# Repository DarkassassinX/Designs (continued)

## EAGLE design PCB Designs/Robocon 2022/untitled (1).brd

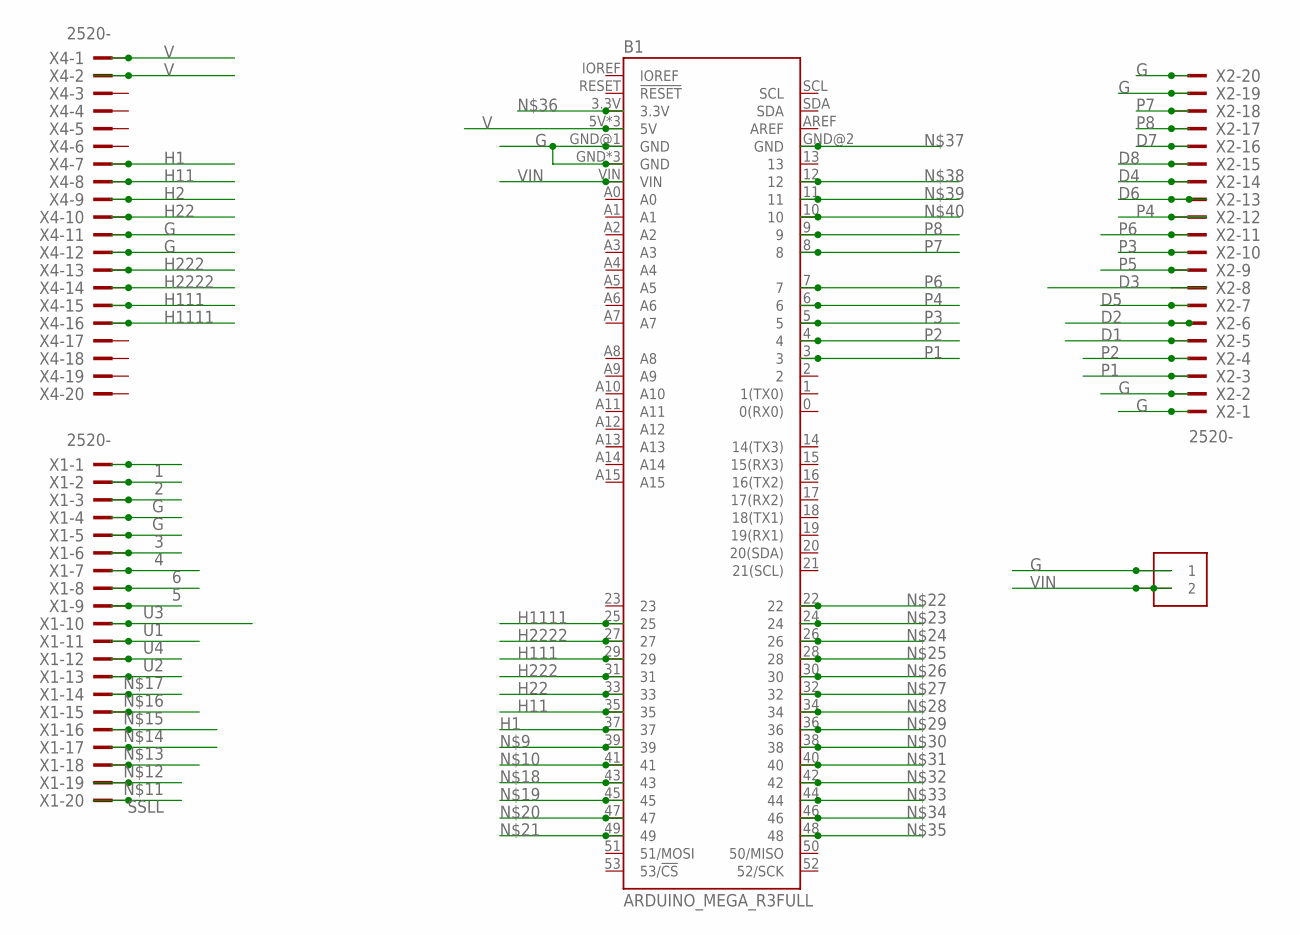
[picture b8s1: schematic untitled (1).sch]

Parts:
B1: ARDUINO_MEGA_R3FULL; ARDUINO_MEGA_NO_SILK
J1: 1X2-3.5MM
X1, X2, X4: 2520-; PAK100/2500-20

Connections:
1: X1.1
2: X1.2
3: X1.5
4: X1.6
5: X1.8
6: X1.7
D1: X2.5
D2: X2.6
D3: X2.8
D4: X2.14
D5: X2.7
D6: X2.13
D7: X2.16
D8: X2.15
G: B1.GND, B1.GND@1 (GND), B1.GND@3 (GND), B1.GND@4 (GND), J1.1, X1.3, X1.4, X2.1, X2.2, X2.19, X2.20, X4.11, X4.12
H1: B1.37, X4.7
H2: X4.9
H11: B1.35, X4.8
H22: B1.33, X4.10
H111: B1.29, X4.15
H222: B1.31, X4.13
H1111: B1.25, X4.16
H2222: B1.27, X4.14
P1: B1.3, X2.3
P2: B1.4, X2.4
P3: B1.5, X2.10
P4: B1.6, X2.12
P5: X2.9
P6: B1.7, X2.11
P7: B1.8, X2.18
P8: B1.9, X2.17
SSLL: X1.20
U1: X1.10
U2: X1.12
U3: X1.9
U4: X1.11
V: B1.5V, B1.5V@1 (5V), B1.5V@2 (5V), X4.1, X4.2
VIN: B1.VIN, J1.2

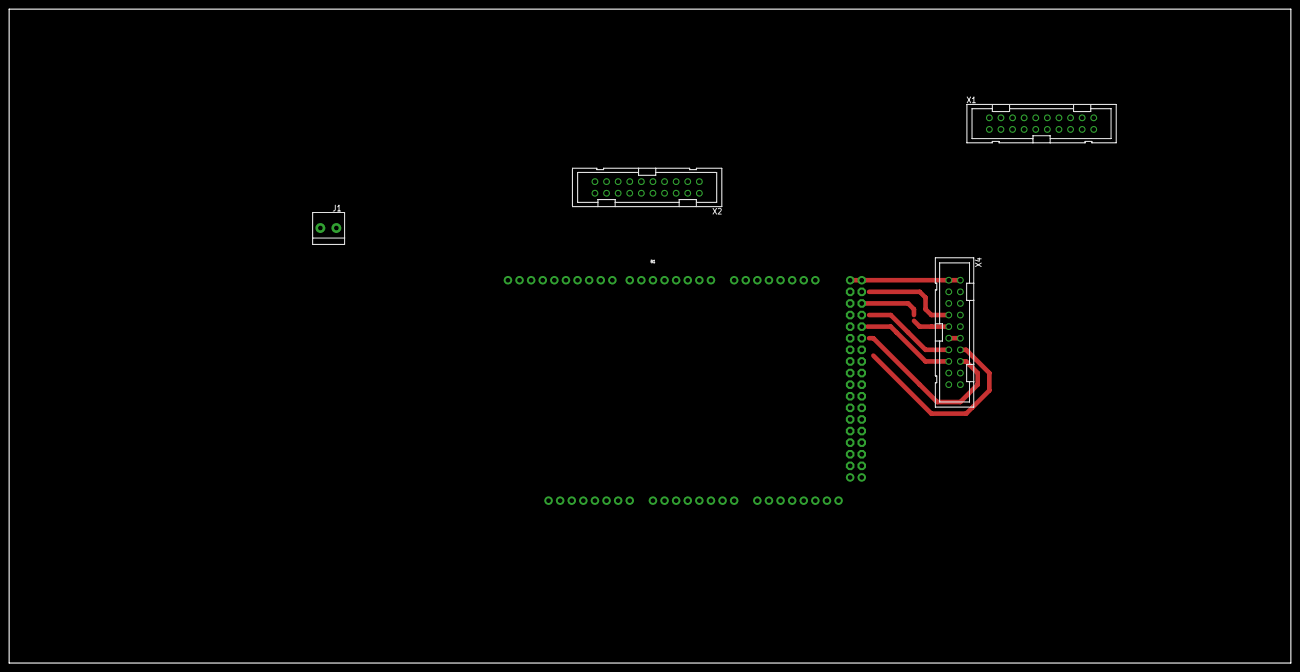
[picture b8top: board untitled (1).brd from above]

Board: 2 copper layers, 280.6 x 143.2 mm, 5 parts (0 on the bottom side), 17 nets.

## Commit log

2022-09-10 CAD Designs and PCB Designs
